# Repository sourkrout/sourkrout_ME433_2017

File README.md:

# sourkrout_ME433_2017
first commit

test

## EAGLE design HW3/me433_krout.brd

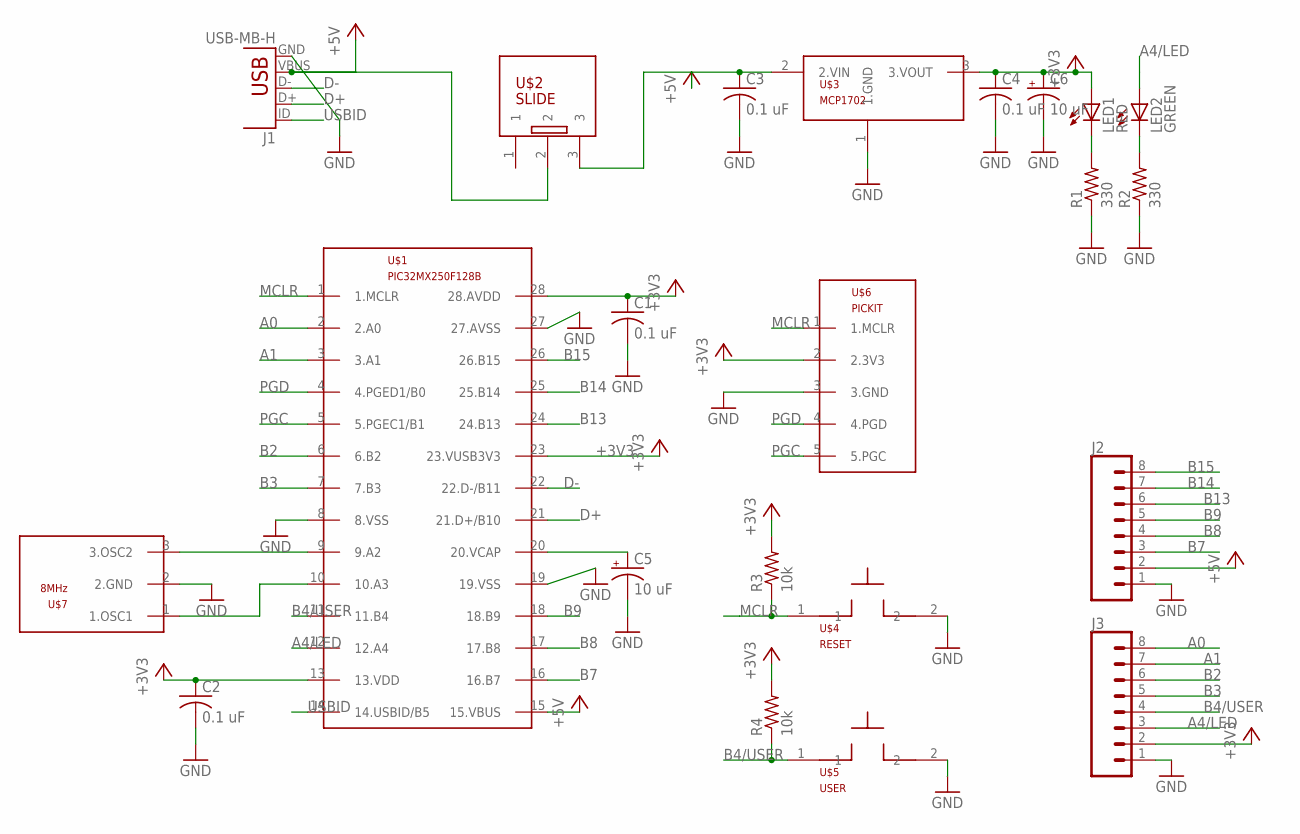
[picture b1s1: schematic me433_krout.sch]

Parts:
C1, C2, C3, C4: 0.1 uF; C025-025X050
C5, C6: 10 uF; B45181B
J1: USB-MB-H
J2, J3: CONN_08"; 1X08
LED1: RED; LED3MM
LED2: GREEN; LED3MM
R1, R2: 330; 0207/10
R3, R4: 10k; 0207/10
U$1: PIC32MX250F128B; DIL28-3
U$2: SLIDE
U$3: MCP1702; TO92
U$4: RESET; PB
U$5: USER; PB
U$6: PICKIT; 1X05
U$7: 8MHz; OSC

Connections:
+3V3: C1.1, C2.1, C4.1, C6.+, J3.2, LED1.A, R3.2, R4.2, U$1.13 (13.VDD), U$1.23 (23.VUSB3V3), U$1.28 (28.AVDD), U$3.3 (3.VOUT), U$6.2 (2.3V3)
+5V: C3.1, J2.2, U$1.15 (15.VBUS), U$2.3, U$3.2 (2.VIN)
A0: J3.8, U$1.2 (2.A0)
A1: J3.7, U$1.3 (3.A1)
A4/LED: J3.3, LED2.A, U$1.12 (12.A4)
B2: J3.6, U$1.6 (6.B2)
B3: J3.5, U$1.7 (7.B3)
B4/USER: J3.4, R4.1, U$1.11 (11.B4), U$5.1
B7: J2.3, U$1.16 (16.B7)
B8: J2.4, U$1.17 (17.B8)
B9: J2.5, U$1.18 (18.B9)
B13: J2.6, U$1.24 (24.B13)
B14: J2.7, U$1.25 (25.B14)
B15: J2.8, U$1.26 (26.B15)
D+: J1.D+, U$1.21 (21.D+/B10)
D-: J1.D-, U$1.22 (22.D-/B11)
GND: C1.2, C2.2, C3.2, C4.2, C5.-, C6.-, J1.GND, J2.1, J3.1, R1.1, R2.1, U$1.8 (8.VSS), U$1.19 (19.VSS), U$1.27 (27.AVSS), U$3.1 (1.GND), U$4.2, U$5.2, U$6.3 (3.GND), U$7.2 (2.GND)
MCLR: R3.1, U$1.1 (1.MCLR), U$4.1, U$6.1 (1.MCLR)
unnamed: LED2.K (C), R2.2
unnamed: C5.+, U$1.20 (20.VCAP)
unnamed: LED1.K (C), R1.2
unnamed: U$1.9 (9.A2), U$7.3 (3.OSC2)
unnamed: U$1.10 (10.A3), U$7.1 (1.OSC1)
PGC: U$1.5 (5.PGEC1/B1), U$6.5 (5.PGC)
PGD: U$1.4 (4.PGED1/B0), U$6.4 (4.PGD)
USBID: J1.ID, U$1.14 (14.USBID/B5)
VBUS: J1.VBUS, U$2.2

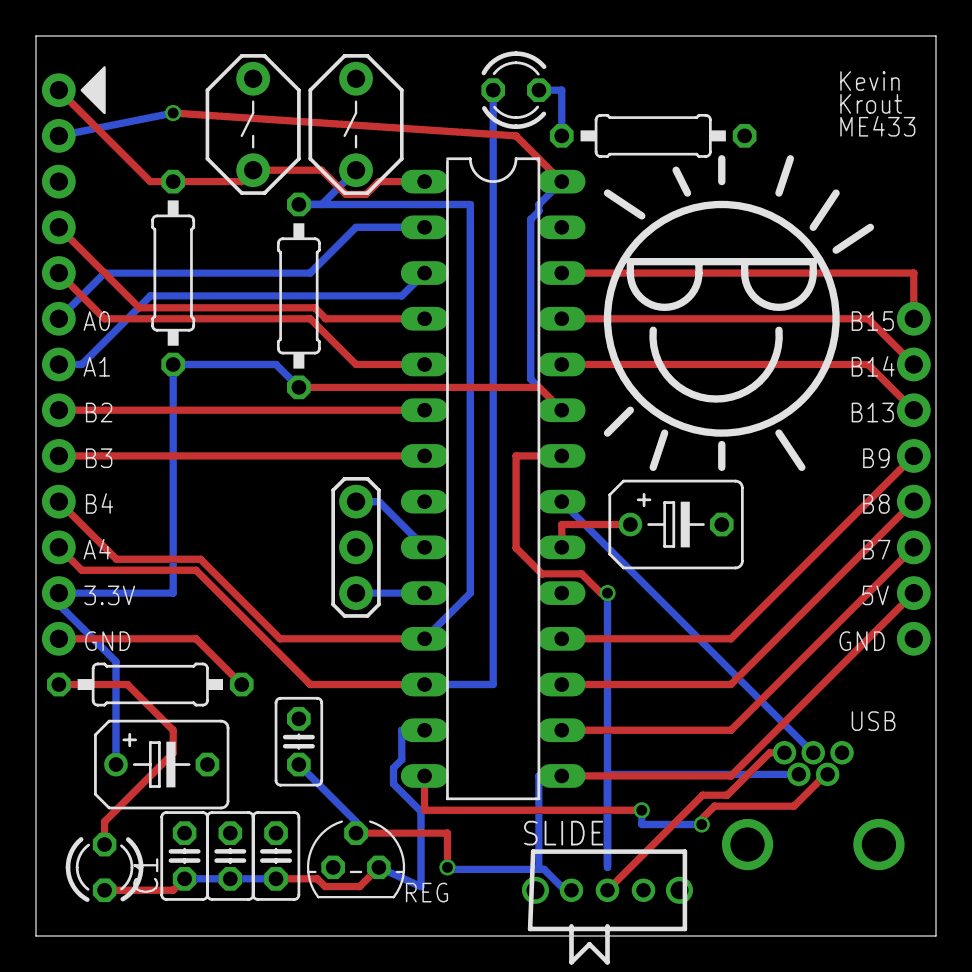
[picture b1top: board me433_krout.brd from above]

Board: 2 copper layers, 50.0 x 50.0 mm, 22 parts (0 on the bottom side), 27 nets.

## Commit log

2017-03-29 testing GitHub desktop
2017-03-29 created HW1 project
2017-03-30 pragma commands
2017-03-30 blinking LED
2017-03-30 wdt fix
2017-03-31 final fix, code works now
2017-03-31 fixed from 500Hz to 1kHz
2017-04-04 Create hw2
2017-04-07 Create HW3
2017-04-07 Add files via upload
    Eagle files for my board
2017-04-07 Add files via upload
    fixed capacitor placement
2017-04-09 started code for hw4
2017-04-09 pragmas and initializations
2017-04-09 full code for spa communication
2017-04-09 fixed timer problem
2017-04-10 almost complete, half sine wave cut off
2017-04-10 fixed bitshifting error, final code working
2017-04-12 HW5 script
2017-04-18 LCD display code
2017-04-18 screen clear test
2017-04-18 working code for LCD
2017-04-20 Writing the 7 accelerometer measurements to the LCD
2017-04-20 bar-drawing
2017-04-20 fully working code
2017-04-24 hw1 code (can't load)
2017-04-25 working harmony code version of HW7
2017-04-27 hw9 test example
2017-04-27 HW9 working
2017-05-09 Working Android HW12 Code
2017-05-11 Green color detector code
2017-05-11 Working code the modifies threshold
2017-05-16 HW10 Code
2017-05-17 Working HID
2017-05-17 HW14 working
2017-06-04 pictures
2017-06-05 hw18 working
2017-06-06 HW19 working
